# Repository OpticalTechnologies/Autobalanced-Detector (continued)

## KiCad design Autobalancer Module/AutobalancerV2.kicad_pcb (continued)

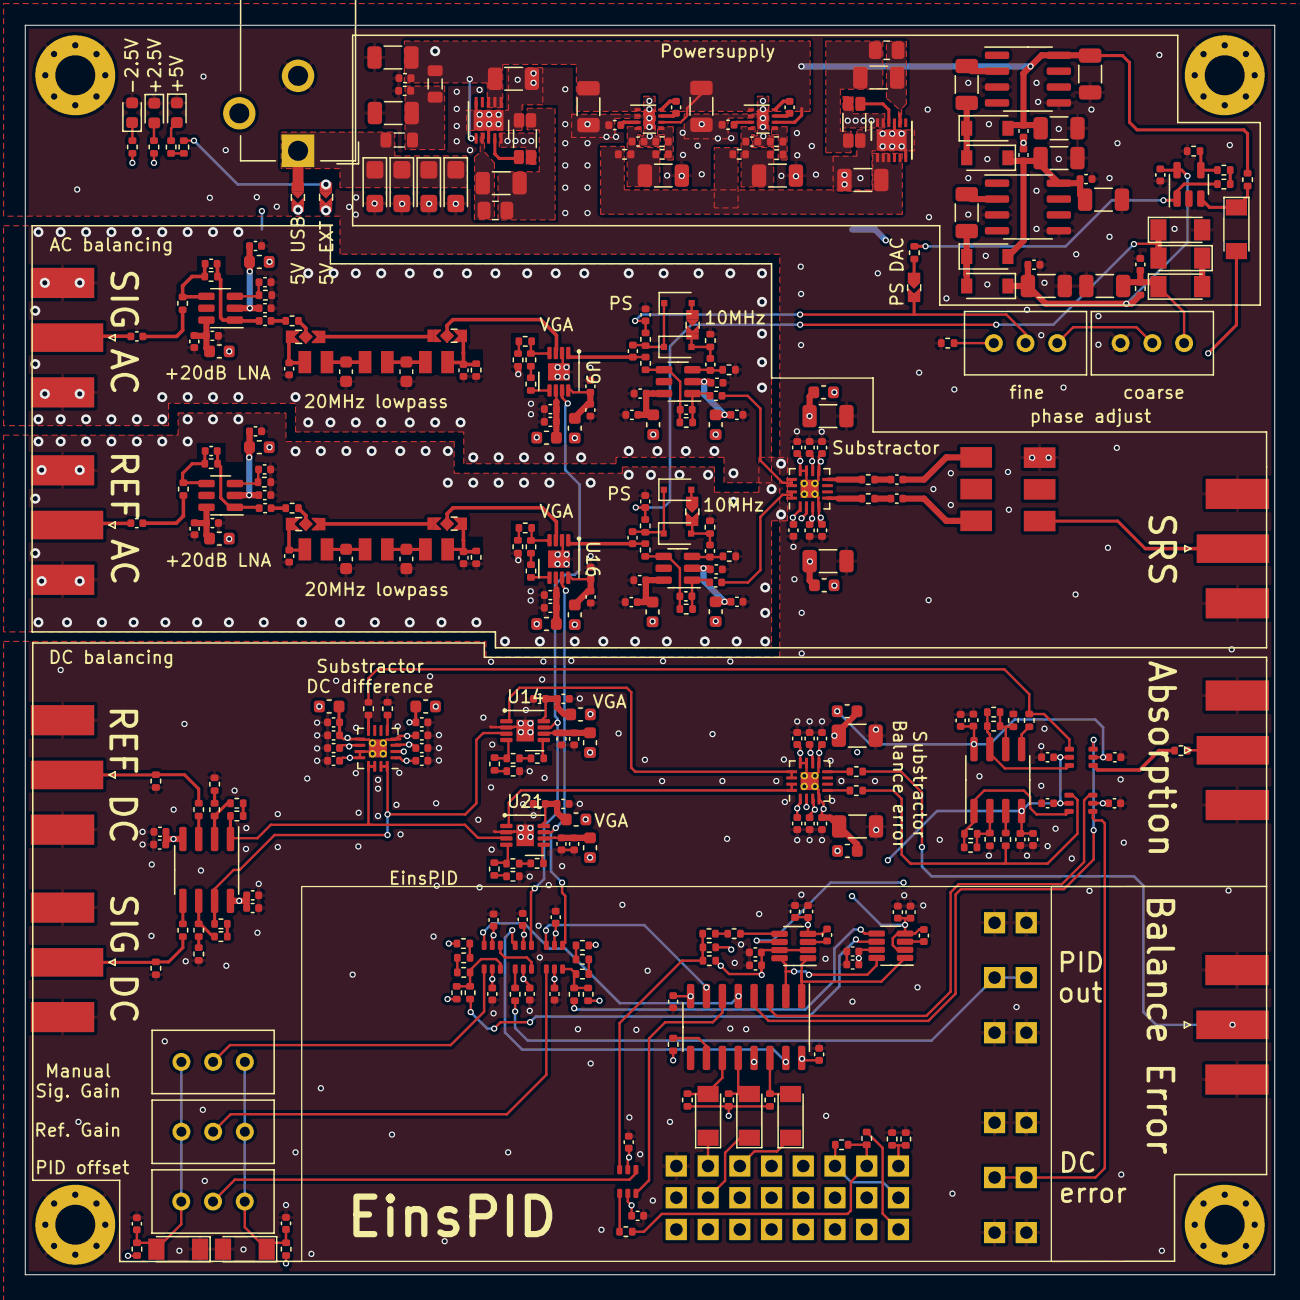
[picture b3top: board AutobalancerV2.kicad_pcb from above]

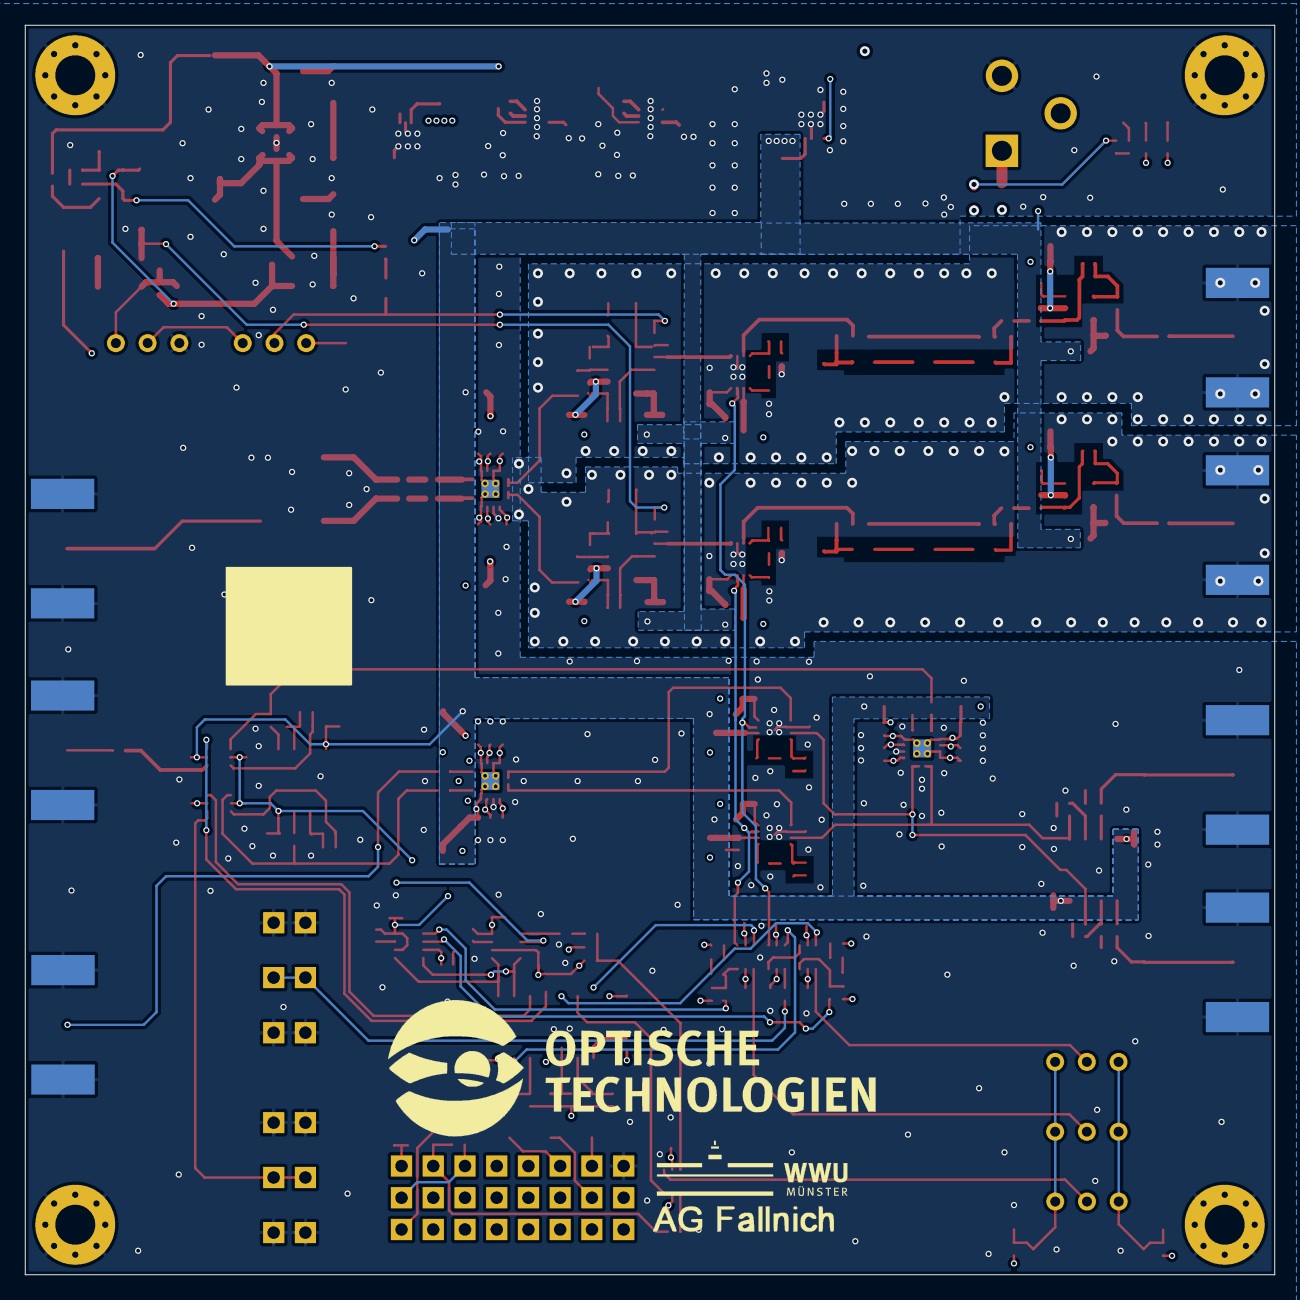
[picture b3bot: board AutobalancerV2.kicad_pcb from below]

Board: 4 copper layers, 100.0 x 100.0 mm, 374 parts (3 on the bottom side), 203 nets.
